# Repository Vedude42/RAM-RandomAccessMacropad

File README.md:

# RAM-RandomAccessMacropad
A macropad that is used for any random keyboard shortcuts and buttons that I dont have on my keyboard

# Schematics

# PCB

# Case

# FirmWare

right now, the firmware is just a numberpad, but when I assemble My macropad I'm going to set it to random miscellaneous shortcuts.

# Bom

You can find the Bom in the PCB Folder (Along with a zip file that you can import straight into jlcpcp for fabrication) with the footprints of the parts. keycaps are DSA 1us

- Seed XIAO RP2040 Microcontroller
- 16x Mechanical switches
- 1x 0.91 inch oled display
- 4 20mm m4 screws
- 16x dsa keycaps

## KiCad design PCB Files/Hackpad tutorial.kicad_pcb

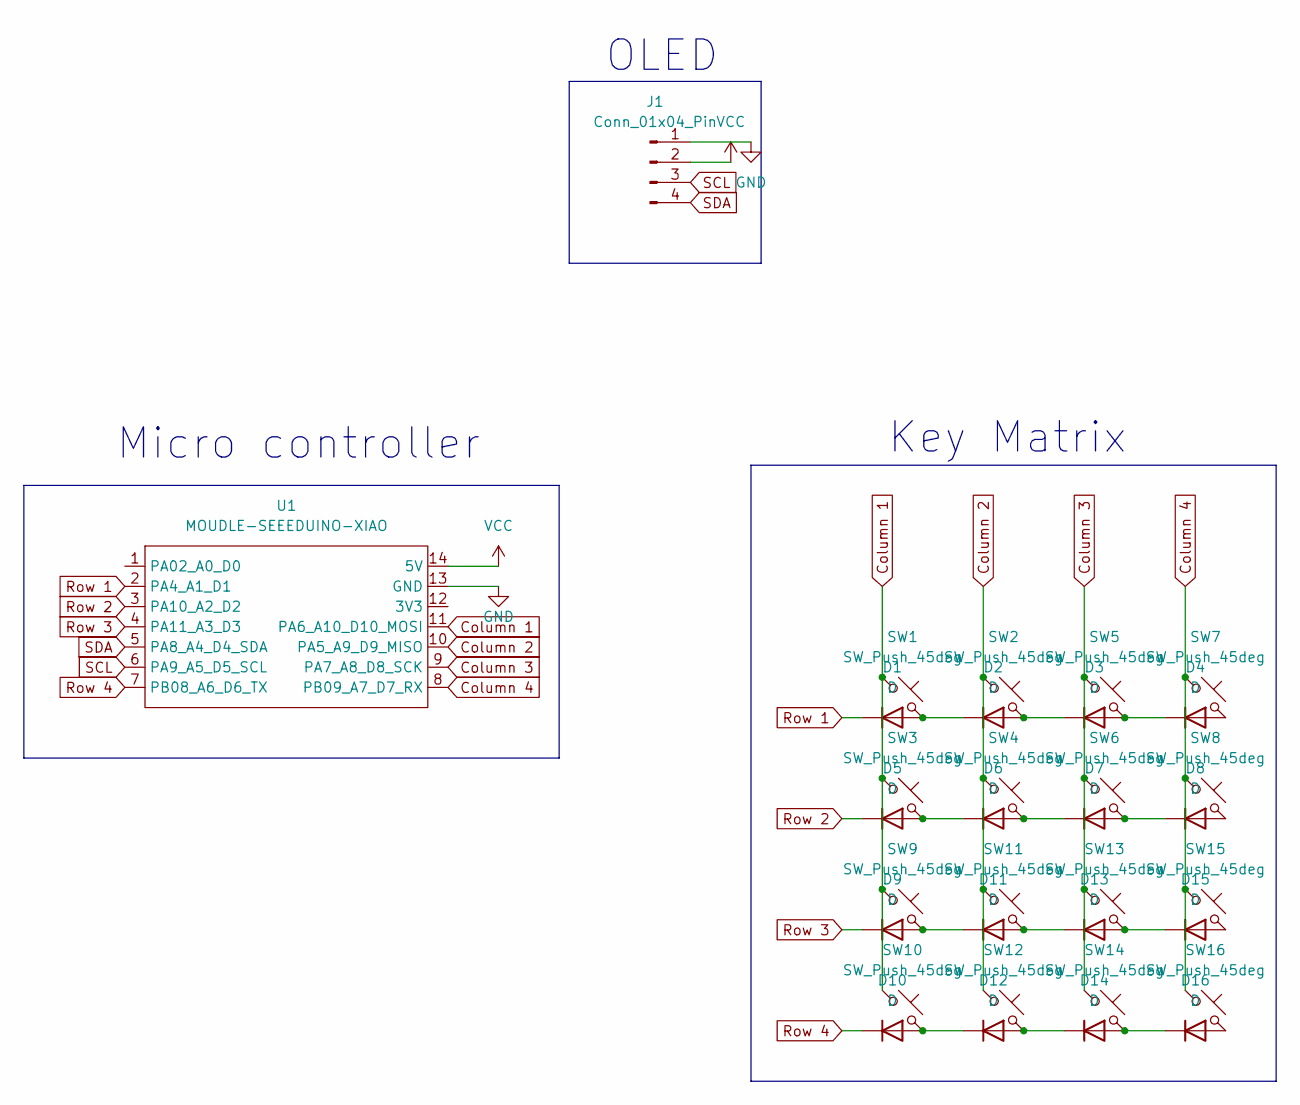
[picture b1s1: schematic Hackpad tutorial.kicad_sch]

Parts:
D1, D2, D3, D4, D5, D6, D7, D8, D9, D10, D11, D12, D13, D14, D15, D16: D; D_DO-35_SOD27_P7.62mm_Horizontal
J1: Conn_01x04_Pin; SSD1306-0.91-OLED-4pin-128x32
SW1, SW2, SW3, SW4, SW5, SW6, SW7, SW8, SW9, SW10, SW11, SW12, SW13, SW14, SW15, SW16: SW_Push_45deg; SW_Cherry_MX_1.00u_PCB
U1: MOUDLE-SEEEDUINO-XIAO; XIAO-Generic-Hybrid-14P-2.54-21X17.8MM

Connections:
Column 1: SW1.1, SW3.1, SW9.1, SW10.1, U1.11 (PA6_A10_D10_MOSI)
Column 2: SW2.1, SW4.1, SW11.1, SW12.1, U1.10 (PA5_A9_D9_MISO)
Column 3: SW5.1, SW6.1, SW13.1, SW14.1, U1.9 (PA7_A8_D8_SCK)
Column 4: SW7.1, SW8.1, SW15.1, SW16.1, U1.8 (PB09_A7_D7_RX)
GND: J1.1, U1.13 (GND)
unnamed: D1.2 (A), D2.1 (K), SW1.2
unnamed: D2.2 (A), D3.1 (K), SW2.2
unnamed: D3.2 (A), D4.1 (K), SW5.2
unnamed: D4.2 (A), SW7.2
unnamed: D5.2 (A), D6.1 (K), SW3.2
unnamed: D6.2 (A), D7.1 (K), SW4.2
unnamed: D7.2 (A), D8.1 (K), SW6.2
unnamed: D8.2 (A), SW8.2
unnamed: D10.2 (A), D12.1 (K), SW10.2
unnamed: D11.2 (A), D13.1 (K), SW11.2
unnamed: D9.2 (A), D11.1 (K), SW9.2
unnamed: D12.2 (A), D14.1 (K), SW12.2
unnamed: D13.2 (A), D15.1 (K), SW13.2
unnamed: D14.2 (A), D16.1 (K), SW14.2
unnamed: D15.2 (A), SW15.2
unnamed: D16.2 (A), SW16.2
Row 1: D1.1 (K), U1.2 (PA4_A1_D1)
Row 2: D5.1 (K), U1.3 (PA10_A2_D2)
Row 3: D9.1 (K), U1.4 (PA11_A3_D3)
Row 4: D10.1 (K), U1.7 (PB08_A6_D6_TX)
SCL: J1.3, U1.6 (PA9_A5_D5_SCL)
SDA: J1.4, U1.5 (PA8_A4_D4_SDA)
VCC: J1.2, U1.14 (5V)

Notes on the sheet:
OLED
Key Matrix
Micro controller

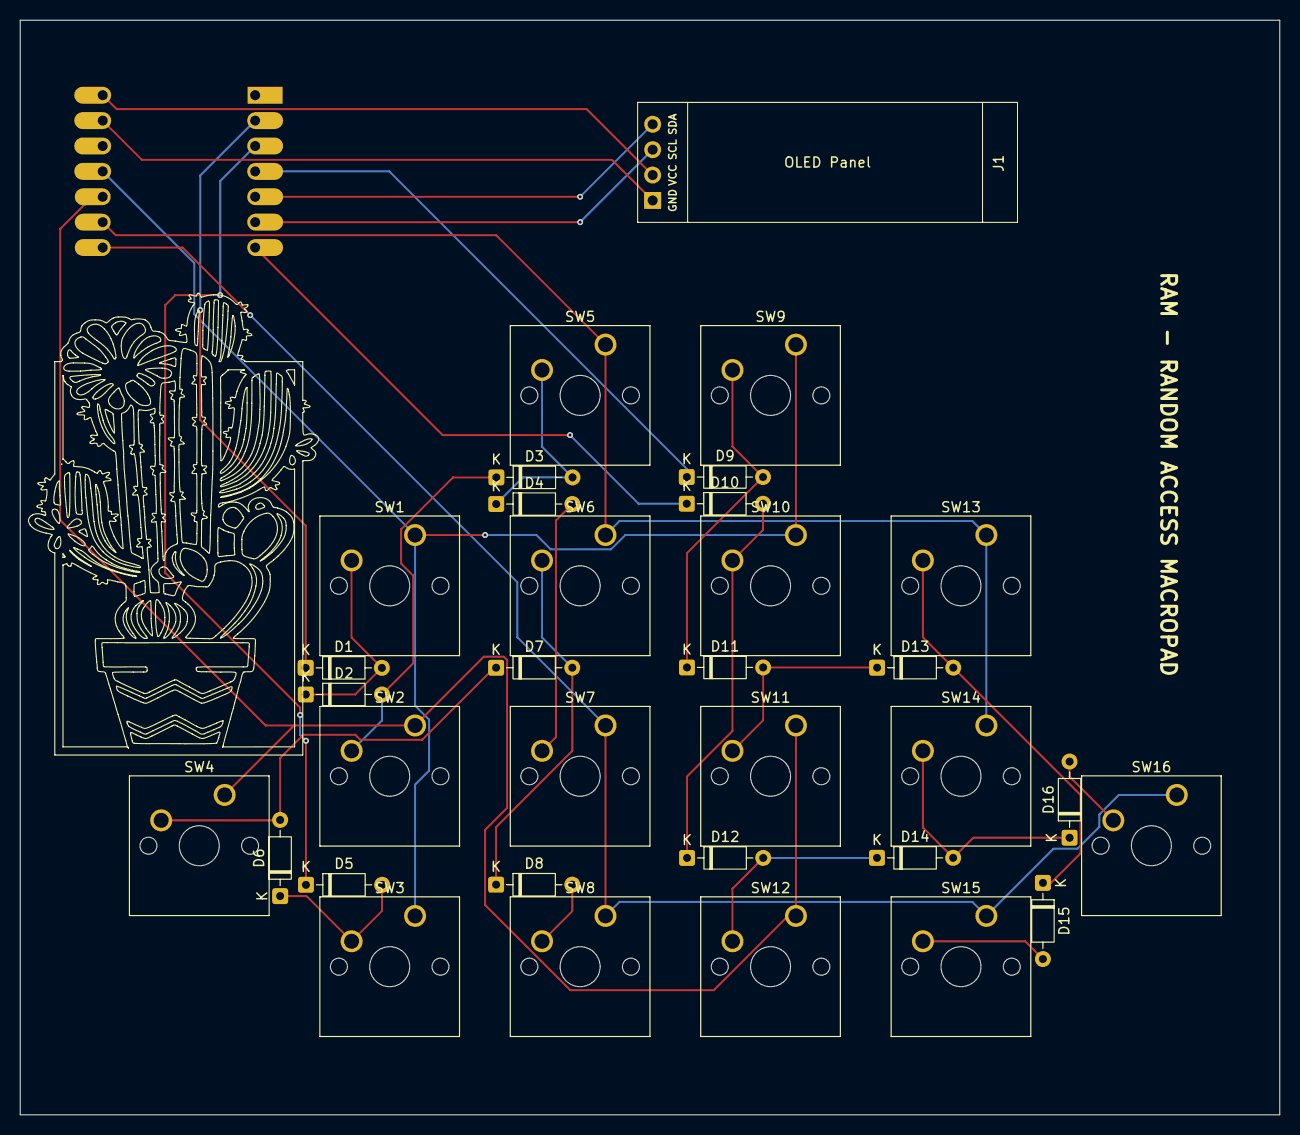
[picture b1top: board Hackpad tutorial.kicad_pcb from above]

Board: 2 copper layers, 126.0 x 109.5 mm, 34 parts (1 on the bottom side), 28 nets.

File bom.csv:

Designator,Footprint,Quantity,Value,LCSC Part #
"D1, D10, D11, D12, D13, D14, D15, D16, D2, D3, D4, D5, D6, D7, D8, D9",D_DO-35_SOD27_P7.62mm_Horizontal,16,D,
J1,SSD1306-0.91-OLED-4pin-128x32,1,Conn_01x04_Pin,
"SW1, SW10, SW11, SW12, SW13, SW14, SW15, SW16, SW2, SW3, SW4, SW5, SW6, SW7, SW8, SW9",SW_Cherry_MX_1.00u_PCB,16,SW_Push_45deg,
U1,XIAO-Generic-Hybrid-14P-2.54-21X17.8MM,1,MOUDLE-SEEEDUINO-XIAO,
